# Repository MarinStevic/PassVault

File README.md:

PassVault

Uređaj dizajniran u sklopu diplomskog rada: https://dabar.srce.hr/islandora/object/etfos%3A3328

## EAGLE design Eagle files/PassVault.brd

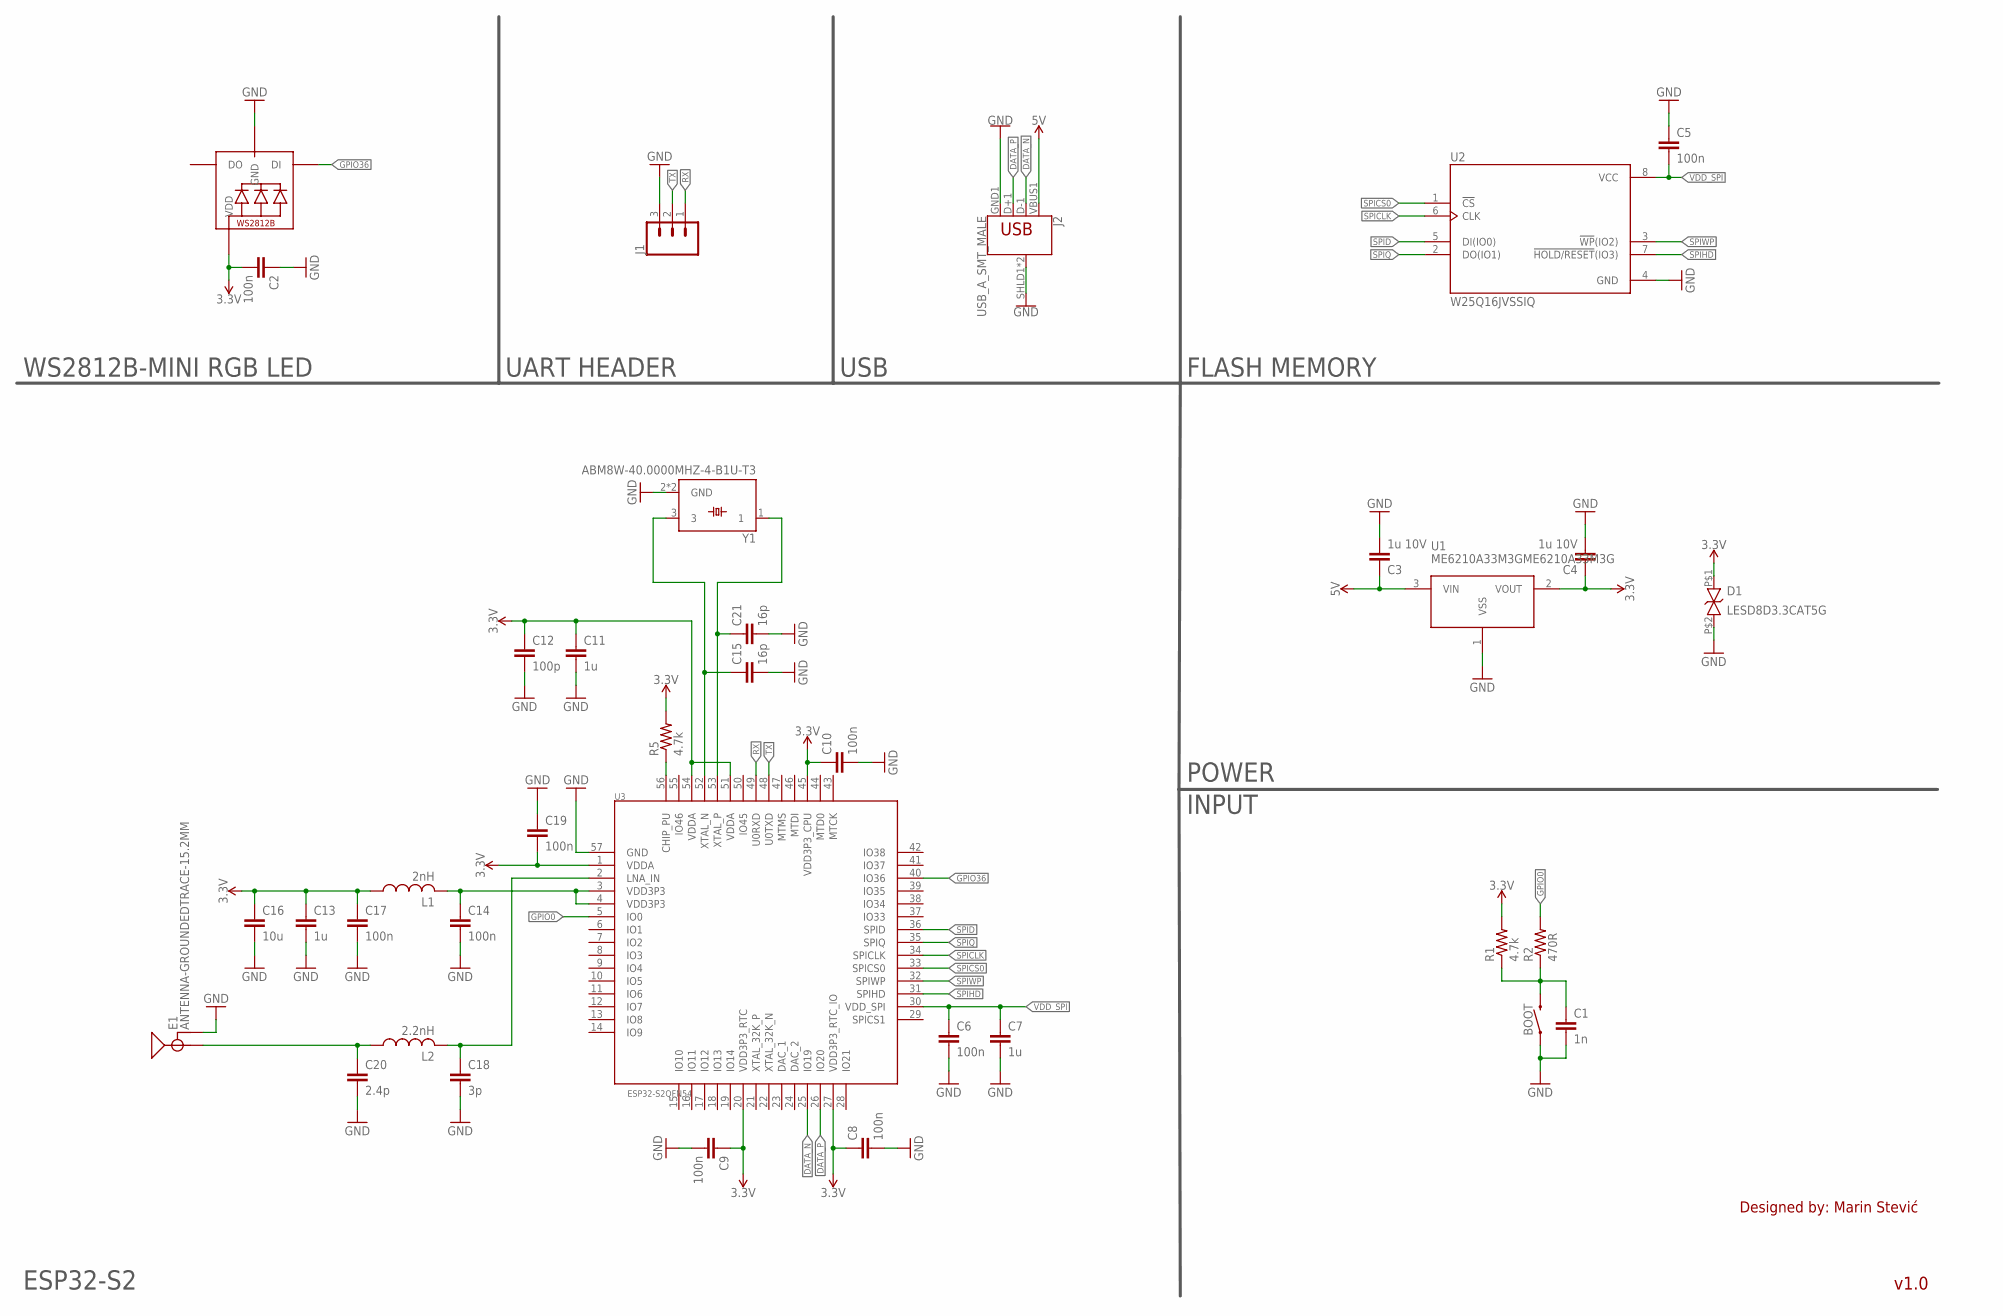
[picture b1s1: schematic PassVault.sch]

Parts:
BOOT: MOMENTARY-SWITCH-SPST-SMD-12MM; TACTILE_SWITCH_SMD_12MM
C1: 1n; C0201
C2: 100n; C0402
C3, C4: 1u 10V; C0402
C5, C6, C8, C9, C10, C14, C17, C19: 100n; C0201
C7, C11, C13: 1u; C0201
C12: 100p; C0201
C15, C21: 16p; C0201
C16: 10u; C0402
C18: 3p; C0201
C20: 2.4p; C0201
D1: LESD8D3.3CAT5G
E1: ANTENNA-GROUNDEDTRACE-15.2MM; TRACE_ANTENNA_2.4GHZ_15.2MM
J1: CONN_03; 1X03
J2: USB_A_SMT_MALE; USB-A-SMT-MALE
L1: 2nH; L0201
L2: 2.2nH; L0201
LED1: WS2812B3535; LED3535
R1, R5: 4.7k; R0201
R2: 470R; R0201
U1: ME6210A33M3GME6210A33M3G; SOT95P280X110-3N
U2: W25Q16JVSSIQ; SOIC127P790X216-8N
U3: ESP32-S2QFN54; QFN40P700X700X90-57T400N
Y1: ABM8W-40.0000MHZ-4-B1U-T3; OSCSC320X250X100N

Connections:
3.3V: C2.2, C4.1, C8.1, C9.1, C10.1, C11.1, C12.1, C13.1, C16.1, C17.1, C19.2, D1.P$1, L1.1, LED1.1 (VDD), R1.2, R5.2, U1.2 (VOUT), U3.1 (VDDA), U3.20 (VDD3P3_RTC), U3.27 (VDD3P3_RTC_IO), U3.45 (VDD3P3_CPU), U3.51 (VDDA), U3.54 (VDDA)
3.3V1: C20.1, E1.ANT (SIGNAL), L2.1
5V: C3.1, J2.VBUS1 (VBUS), U1.3 (VIN)
DATA_N: J2.D-1 (D-), U3.25 (IO19)
DATA_P: J2.D+1 (D+), U3.26 (IO20)
GND: BOOT.1, C1.2, C2.1, C3.2, C4.2, C5.1, C6.2, C7.2, C8.2, C9.2, C10.2, C11.2, C12.2, C13.2, C14.2, C15.2, C16.2, C17.2, C18.2, C19.1, C20.2, C21.2, D1.P$2, E1.GND, J1.3, J2.GND1 (GND), J2.SHLD1 (SHIELD), J2.SHLD2 (SHIELD), LED1.3 (GND), U1.1 (VSS), U2.4 (GND), U3.57 (GND), Y1.2 (GND), Y1.4 (GND)
GPIO0: R2.2, U3.5 (IO0)
GPIO36: LED1.4 (DI), U3.40 (IO36)
unnamed: R5.1, U3.56 (CHIP_PU)
unnamed: BOOT.3 (2), C1.1, R1.1, R2.1
unnamed: C14.1, L1.2, U3.3 (VDD3P3), U3.4 (VDD3P3)
unnamed: C15.1, U3.52 (XTAL_N), Y1.3
unnamed: C21.1, U3.53 (XTAL_P), Y1.1
unnamed: C18.1, L2.2, U3.2 (LNA_IN)
RX: J1.1, U3.49 (U0RXD)
SPICLK: U2.6 (CLK), U3.34 (SPICLK)
SPICS0: U2.1 (!CS), U3.33 (SPICS0)
SPID: U2.5 (DI(IO0)), U3.36 (SPID)
SPIHD: U2.7 (!HOLD/RESET!(IO3)), U3.31 (SPIHD)
SPIQ: U2.2 (DO(IO1)), U3.35 (SPIQ)
SPIWP: U2.3 (!WP!(IO2)), U3.32 (SPIWP)
TX: J1.2, U3.48 (U0TXD)
VDD_SPI: C5.2, C6.1, C7.1, U2.8 (VCC), U3.30 (VDD_SPI)

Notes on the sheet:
WS2812B-MINI RGB LED
UART HEADER
USB
FLASH MEMORY
POWER
INPUT
ESP32-S2
v1.0
Designed by: Marin Stević

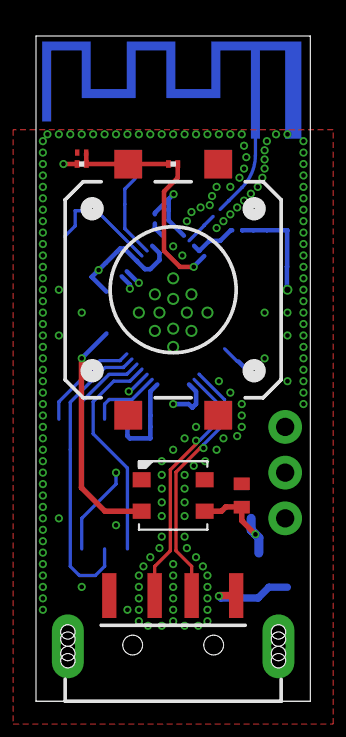
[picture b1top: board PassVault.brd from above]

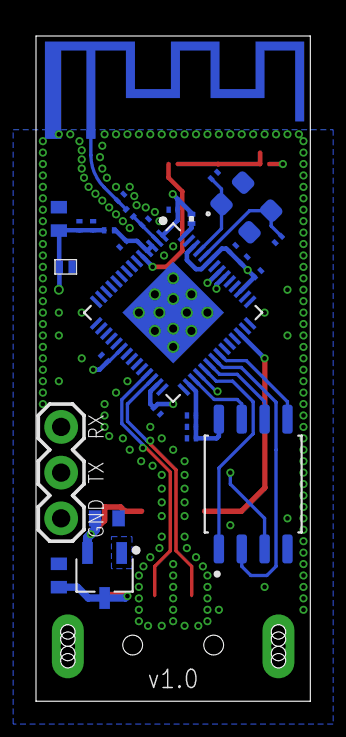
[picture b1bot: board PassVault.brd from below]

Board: 4 copper layers, 15.2 x 37.0 mm, 36 parts (29 on the bottom side), 23 nets.

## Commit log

2021-11-04 Initial upload

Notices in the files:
parts and their libraries:
SparkFun-Switches: Licensing: Creative Commons ShareAlike 4.0 International - https://creativecommons.org/licenses/by-sa/4.0
